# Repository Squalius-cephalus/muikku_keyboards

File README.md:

# Muikku58

Muikku58 is a RP2040 based 56-key column staggered split keyboard, that uses Redragon low profile switches. Design is inspired from REVIUNG41 and Corne keyboards.

## Bill of materials

 - 2 x Muikku58 PCB
 - 2 x RP2040 Zero
 - 2 x 3D printed case
 - 2 x 3D printed plate
 - 2 x 3D printed MCU cover
 - 2 x EC11 Rotary encoders
 - 2  x TRRS connector(PJ320D)
 - 56 x Redragon low profile switches
 - 56 x Low profile MX compatible keycaps
 - 58 x 1N4148 Diodes or 1N4148W SOD-123
 - 22 x M2 4mm bolt
 - 22 x M2 brass inserts(M2xL3xOD3.2)
 - 12 x Rubber feet

# Muikku18

Muikku18 is a 16-key macro pad, that also uses Redragon low profile switches. 

## Bill of materials

 - 1 x Muikku18 PCB
 - 1 x RP2040 Zero
 - 1 x 3D printed case
 - 1 x 3D printed plate
 - 1 x 3D printed MCU cover
 - 2 x EC11 Rotary encoders
 - 16 x Redragon low profile switches
 - 16 x Low profile MX compatible keycaps
 - 18 x 1N4148 Diodes or 1N4148W SOD-123
 - 5 x M2 4mm bolt
 - 5 x M2 brass inserts(M2xL3xOD3.2)
 - 6 x Rubber feet

Both PCB design uses footprints from [ScottoKeebs](https://github.com/joe-scotto/scottokeebs/tree/main/Extras/ScottoKicad "ScottoKeebs") and [kbd library.](https://github.com/foostan/kbd "kbd library.")

Redragon switch footprint is from [keyboard-labs repository.](https://github.com/rgoulter/keyboard-labs "keyboard-labs")

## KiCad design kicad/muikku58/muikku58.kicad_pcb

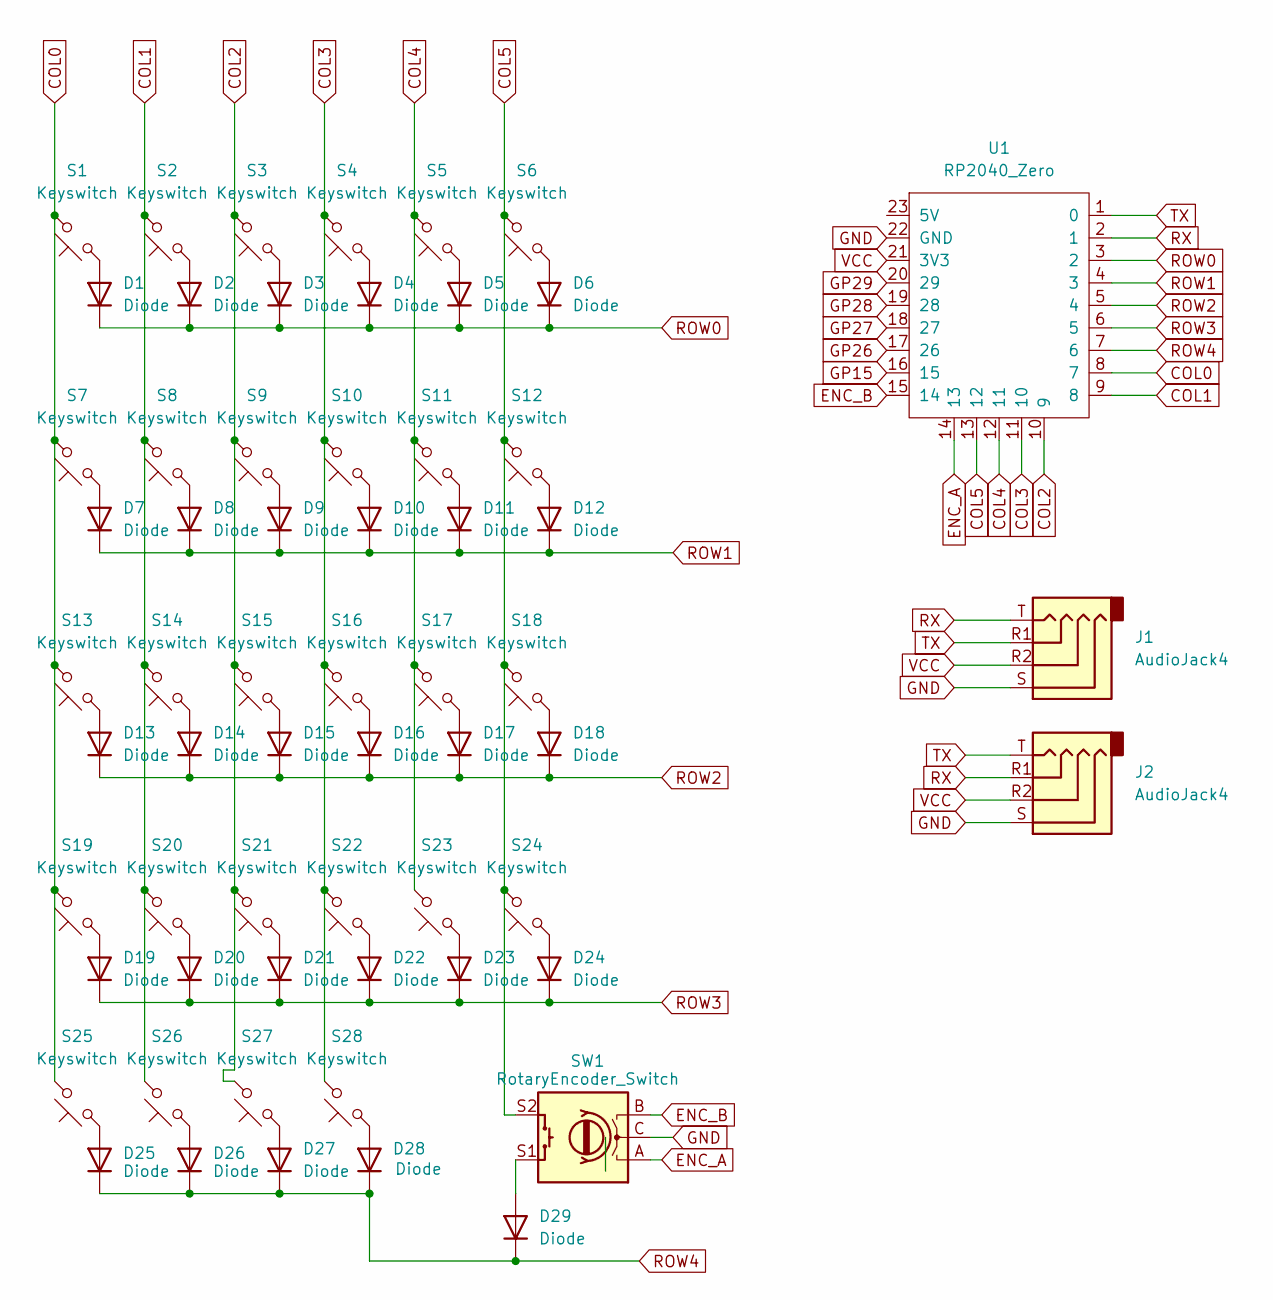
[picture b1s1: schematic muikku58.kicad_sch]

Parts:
D1, D2, D3, D4, D5, D6, D7, D8, D9, D10, D11, D12, D13, D14, D15, D16, D17, D18, D19, D20, D21, D22, D23, D24, D25, D26, D27, D28, D29: Diode; D3_TH_SMD_v2
J1, J2: AudioJack4; Jack_3.5mm_PJ320D_Horizontal
S1, S2, S3, S4, S5, S6, S7, S8, S9, S10, S11, S12, S13, S14, S15, S16, S17, S18, S19, S20, S21, S22, S23, S24, S25, S26, S27, S28: Keyswitch; SW_Redragon_LowProfile_PCB_1.00u_REV
SW1: RotaryEncoder_Switch; RotaryEncoder_Alps_EC11E-Switch_Vertical_H20mm
U1: RP2040_Zero

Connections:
COL0: S1.2, S7.2, S13.2, S19.2, S25.2, U1.8 (7)
COL1: S2.2, S8.2, S14.2, S20.2, S26.2, U1.9 (8)
COL2: S3.2, S9.2, S15.2, S21.2, S27.2, U1.10 (9)
COL3: S4.2, S10.2, S16.2, S22.2, S28.2, U1.11 (10)
COL4: S5.2, S11.2, S17.2, S23.2, U1.12 (11)
COL5: S6.2, S12.2, S18.2, S24.2, SW1.S2, U1.13 (12)
ENC_A: SW1.A, U1.14 (13)
ENC_B: SW1.B, U1.15 (14)
GND: J1.S, J2.S, SW1.C, U1.22 (GND)
GP15: U1.16 (15)
GP26: U1.17 (26)
GP27: U1.18 (27)
GP28: U1.19 (28)
GP29: U1.20 (29)
unnamed: D1.2 (A), S1.1
unnamed: D2.2 (A), S2.1
unnamed: D3.2 (A), S3.1
unnamed: D4.2 (A), S4.1
unnamed: D5.2 (A), S5.1
unnamed: D6.2 (A), S6.1
unnamed: D7.2 (A), S7.1
unnamed: D8.2 (A), S8.1
unnamed: D9.2 (A), S9.1
unnamed: D10.2 (A), S10.1
unnamed: D11.2 (A), S11.1
unnamed: D12.2 (A), S12.1
unnamed: D13.2 (A), S13.1
unnamed: D14.2 (A), S14.1
unnamed: D15.2 (A), S15.1
unnamed: D16.2 (A), S16.1
unnamed: D17.2 (A), S17.1
unnamed: D18.2 (A), S18.1
unnamed: D19.2 (A), S19.1
unnamed: D20.2 (A), S20.1
unnamed: D21.2 (A), S21.1
unnamed: D22.2 (A), S22.1
unnamed: D23.2 (A), S23.1
unnamed: D24.2 (A), S24.1
unnamed: D25.2 (A), S25.1
unnamed: D26.2 (A), S26.1
unnamed: D27.2 (A), S27.1
unnamed: D28.2 (A), S28.1
unnamed: D29.2 (A), SW1.S1
ROW0: D1.1 (K), D2.1 (K), D3.1 (K), D4.1 (K), D5.1 (K), D6.1 (K), U1.3 (2)
ROW1: D7.1 (K), D8.1 (K), D9.1 (K), D10.1 (K), D11.1 (K), D12.1 (K), U1.4 (3)
ROW2: D13.1 (K), D14.1 (K), D15.1 (K), D16.1 (K), D17.1 (K), D18.1 (K), U1.5 (4)
ROW3: D19.1 (K), D20.1 (K), D21.1 (K), D22.1 (K), D23.1 (K), D24.1 (K), U1.6 (5)
ROW4: D25.1 (K), D26.1 (K), D27.1 (K), D28.1 (K), D29.1 (K), U1.7 (6)
RX: J1.T, J2.R1, U1.2 (1)
TX: J1.R1, J2.T, U1.1 (0)
VCC: J1.R2, J2.R2, U1.21 (3V3)

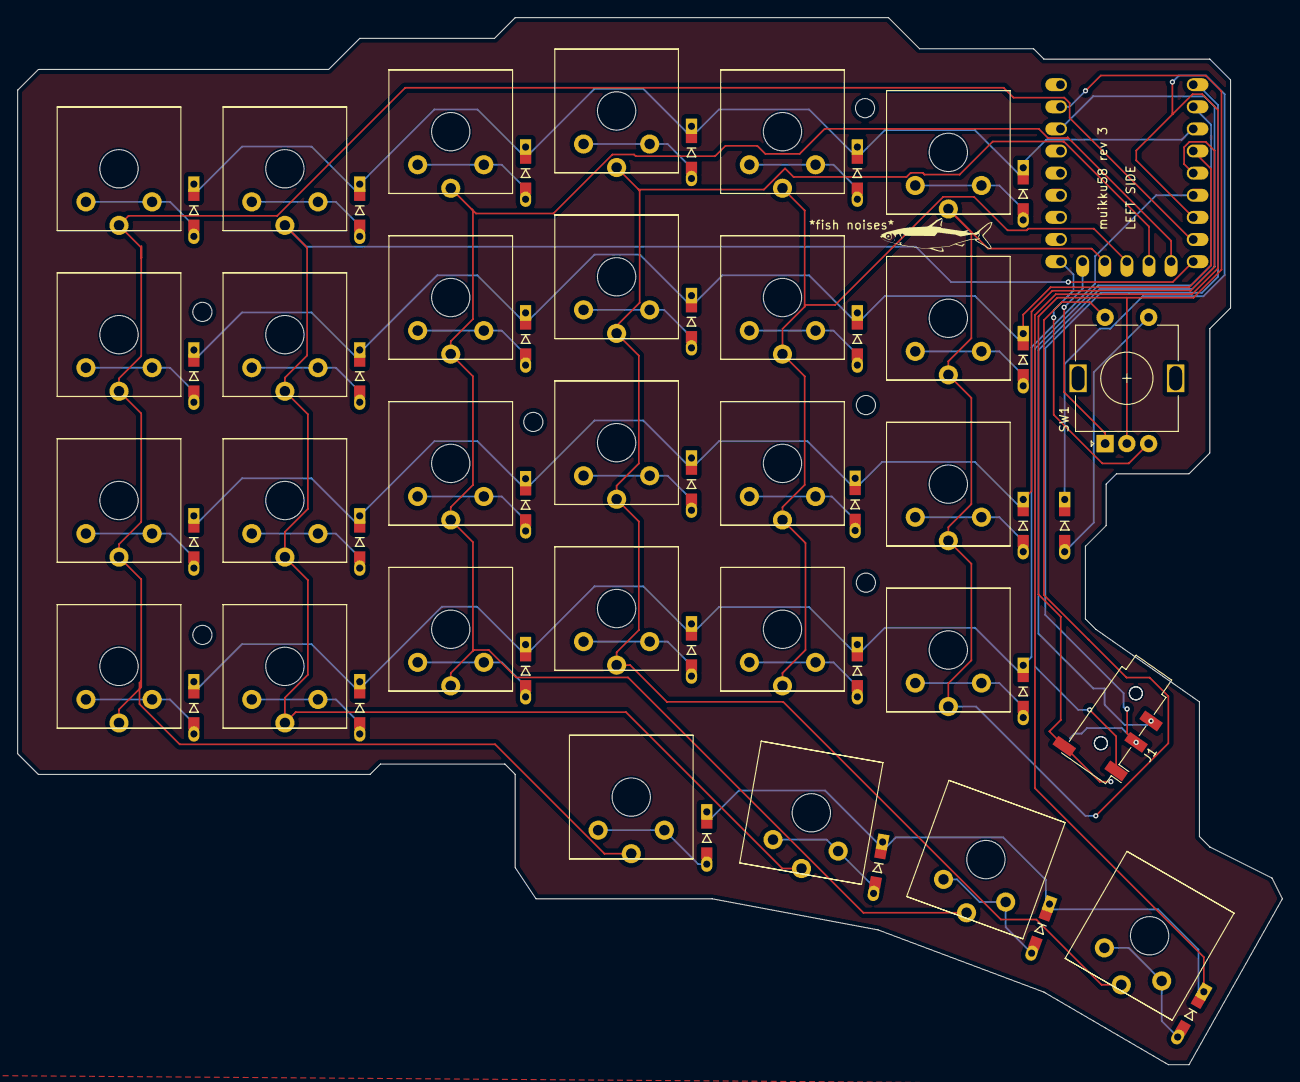
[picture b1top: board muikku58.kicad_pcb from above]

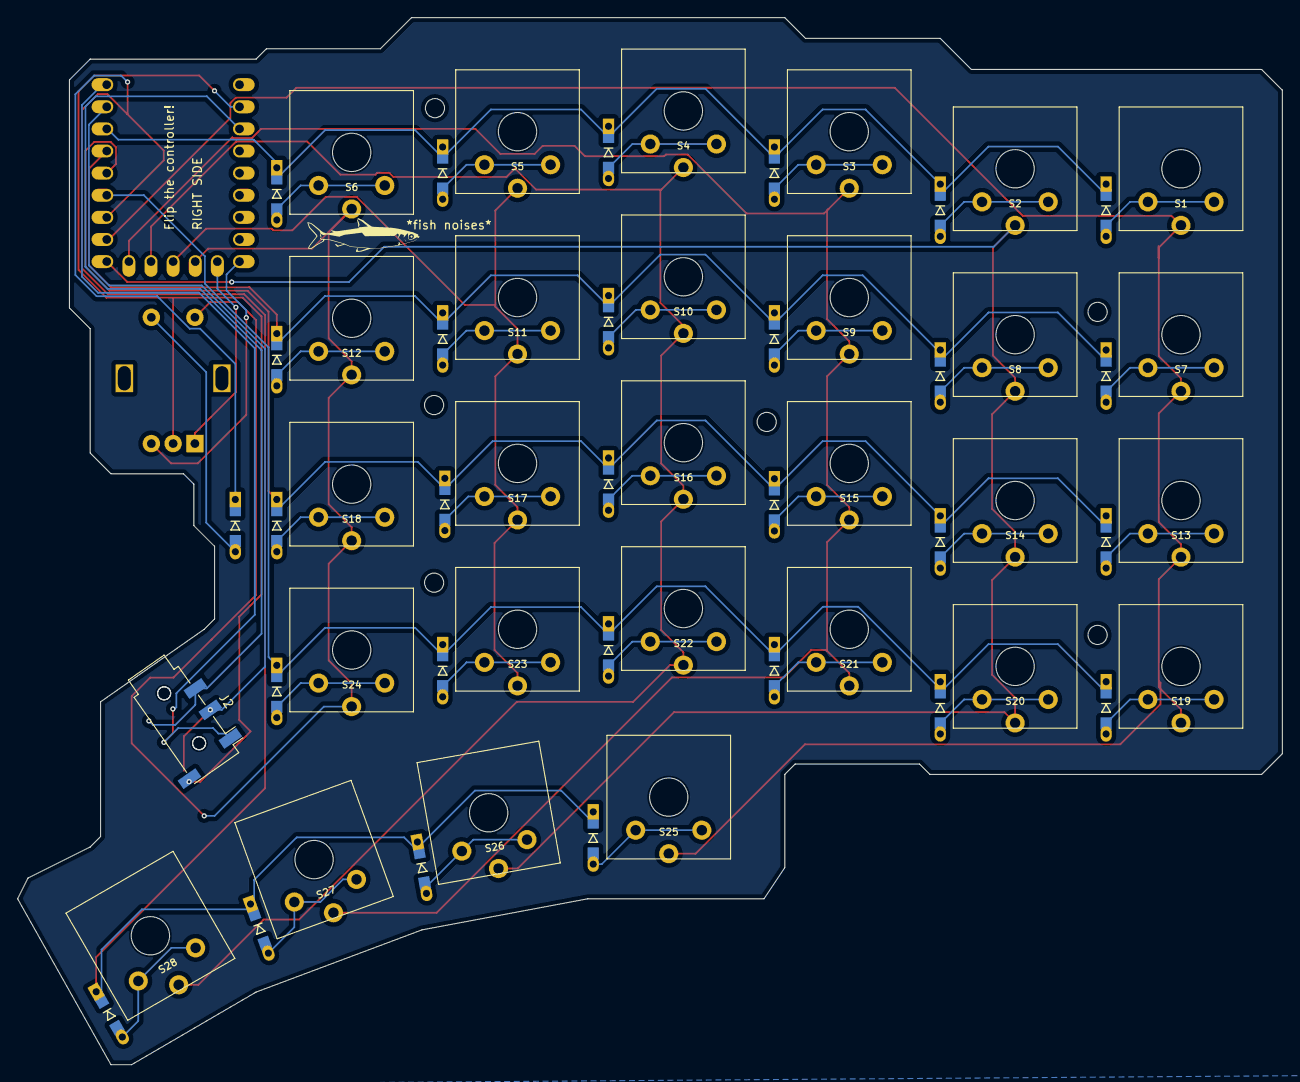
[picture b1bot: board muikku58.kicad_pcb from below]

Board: 2 copper layers, 145.3 x 120.3 mm, 61 parts (30 on the bottom side), 46 nets.

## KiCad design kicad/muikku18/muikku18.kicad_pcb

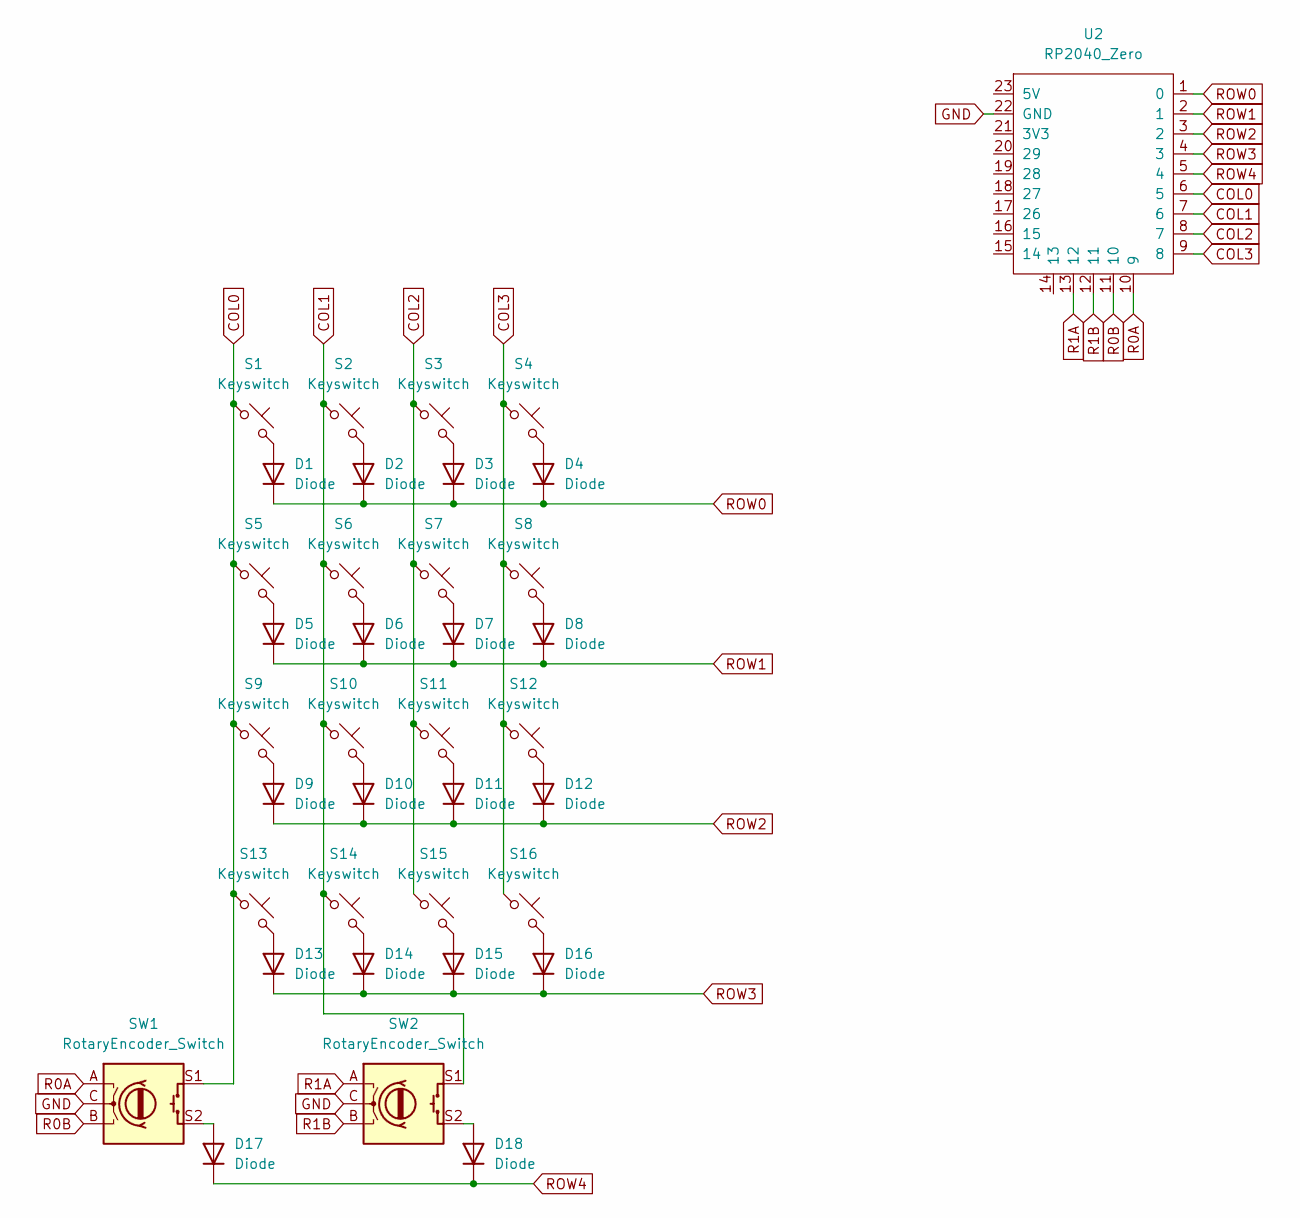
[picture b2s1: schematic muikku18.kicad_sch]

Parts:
D1, D2, D3, D4, D5, D6, D7, D8, D9, D10, D11, D12, D13, D14, D15, D16, D17, D18: Diode; D3_TH_SMD_v2
S1, S2, S3, S4, S5, S6, S7, S8, S9, S10, S11, S12, S13, S14, S15, S16: Keyswitch; SW_Redragon_LowProfile_PCB_1.00u
SW1, SW2: RotaryEncoder_Switch; RotaryEncoder_Alps_EC11E-Switch_Vertical_H20mm
U2: RP2040_Zero

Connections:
COL0: S1.1, S5.1, S9.1, S13.1, SW1.S1, U2.6 (5)
COL1: S2.1, S6.1, S10.1, S14.1, SW2.S1, U2.7 (6)
COL2: S3.1, S7.1, S11.1, S15.1, U2.8 (7)
COL3: S4.1, S8.1, S12.1, S16.1, U2.9 (8)
GND: SW1.C, SW2.C, U2.22 (GND)
unnamed: D1.2 (A), S1.2
unnamed: D2.2 (A), S2.2
unnamed: D3.2 (A), S3.2
unnamed: D4.2 (A), S4.2
unnamed: D5.2 (A), S5.2
unnamed: D6.2 (A), S6.2
unnamed: D7.2 (A), S7.2
unnamed: D8.2 (A), S8.2
unnamed: D9.2 (A), S9.2
unnamed: D10.2 (A), S10.2
unnamed: D11.2 (A), S11.2
unnamed: D12.2 (A), S12.2
unnamed: D13.2 (A), S13.2
unnamed: D14.2 (A), S14.2
unnamed: D15.2 (A), S15.2
unnamed: D16.2 (A), S16.2
unnamed: D17.2 (A), SW1.S2
unnamed: D18.2 (A), SW2.S2
R0A: SW1.A, U2.10 (9)
R0B: SW1.B, U2.11 (10)
R1A: SW2.A, U2.13 (12)
R1B: SW2.B, U2.12 (11)
ROW0: D1.1 (K), D2.1 (K), D3.1 (K), D4.1 (K), U2.1 (0)
ROW1: D5.1 (K), D6.1 (K), D7.1 (K), D8.1 (K), U2.2 (1)
ROW2: D9.1 (K), D10.1 (K), D11.1 (K), D12.1 (K), U2.3 (2)
ROW3: D13.1 (K), D14.1 (K), D15.1 (K), D16.1 (K), U2.4 (3)
ROW4: D17.1 (K), D18.1 (K), U2.5 (4)

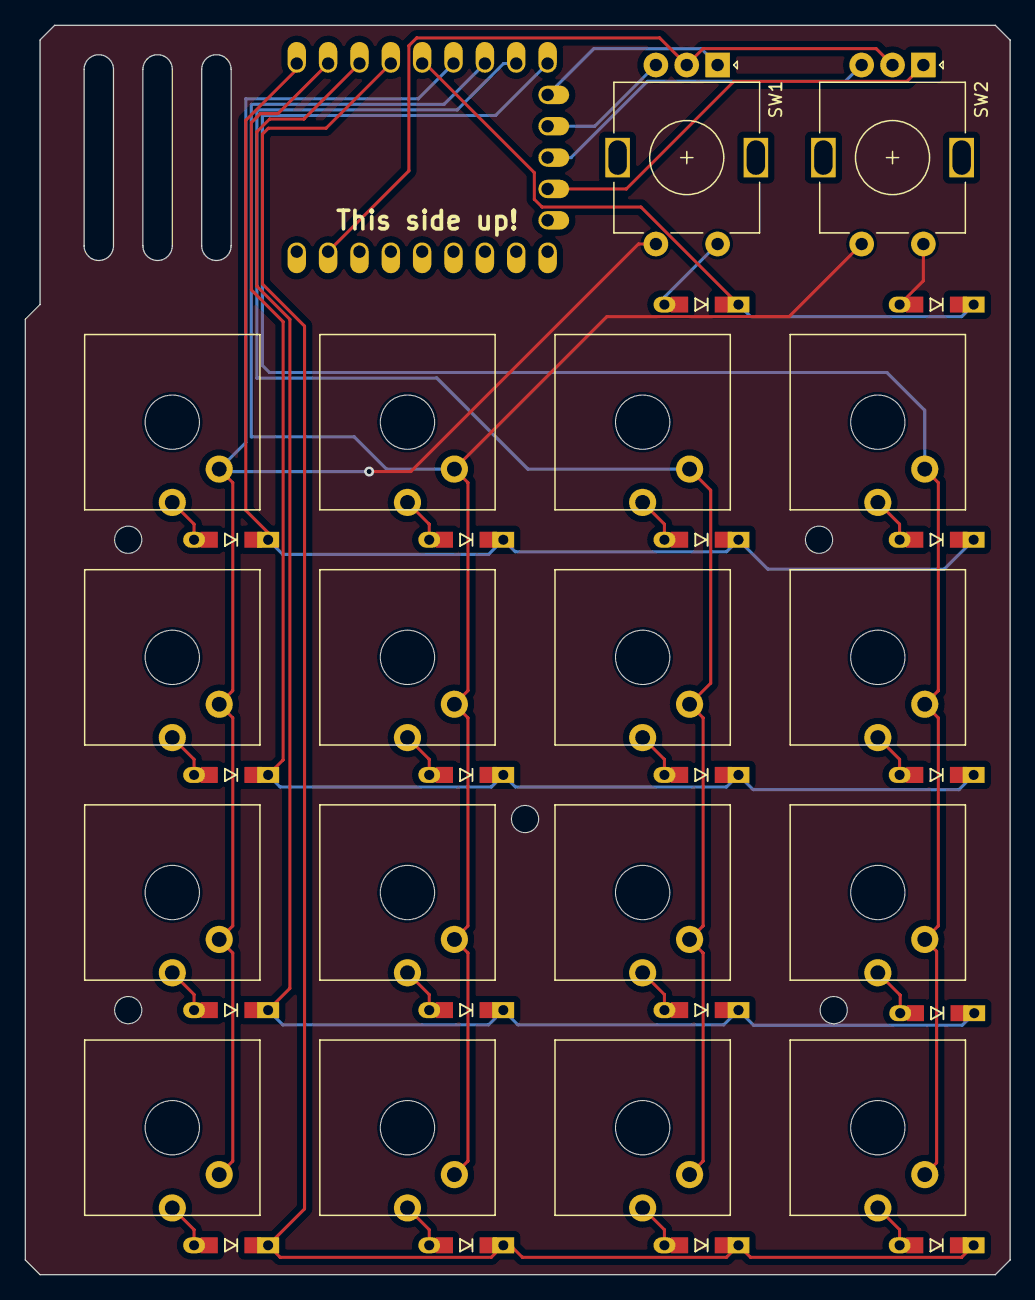
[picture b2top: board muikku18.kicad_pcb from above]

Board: 2 copper layers, 79.8 x 101.2 mm, 37 parts (0 on the bottom side), 32 nets.

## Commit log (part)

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2025-03-31 Firmware added
2025-04-02 Added case STL and fixed the both keyboards UID
2025-04-07 Fixed the encoder mapping
2025-05-27 Fixed trace near the TRRS connector
